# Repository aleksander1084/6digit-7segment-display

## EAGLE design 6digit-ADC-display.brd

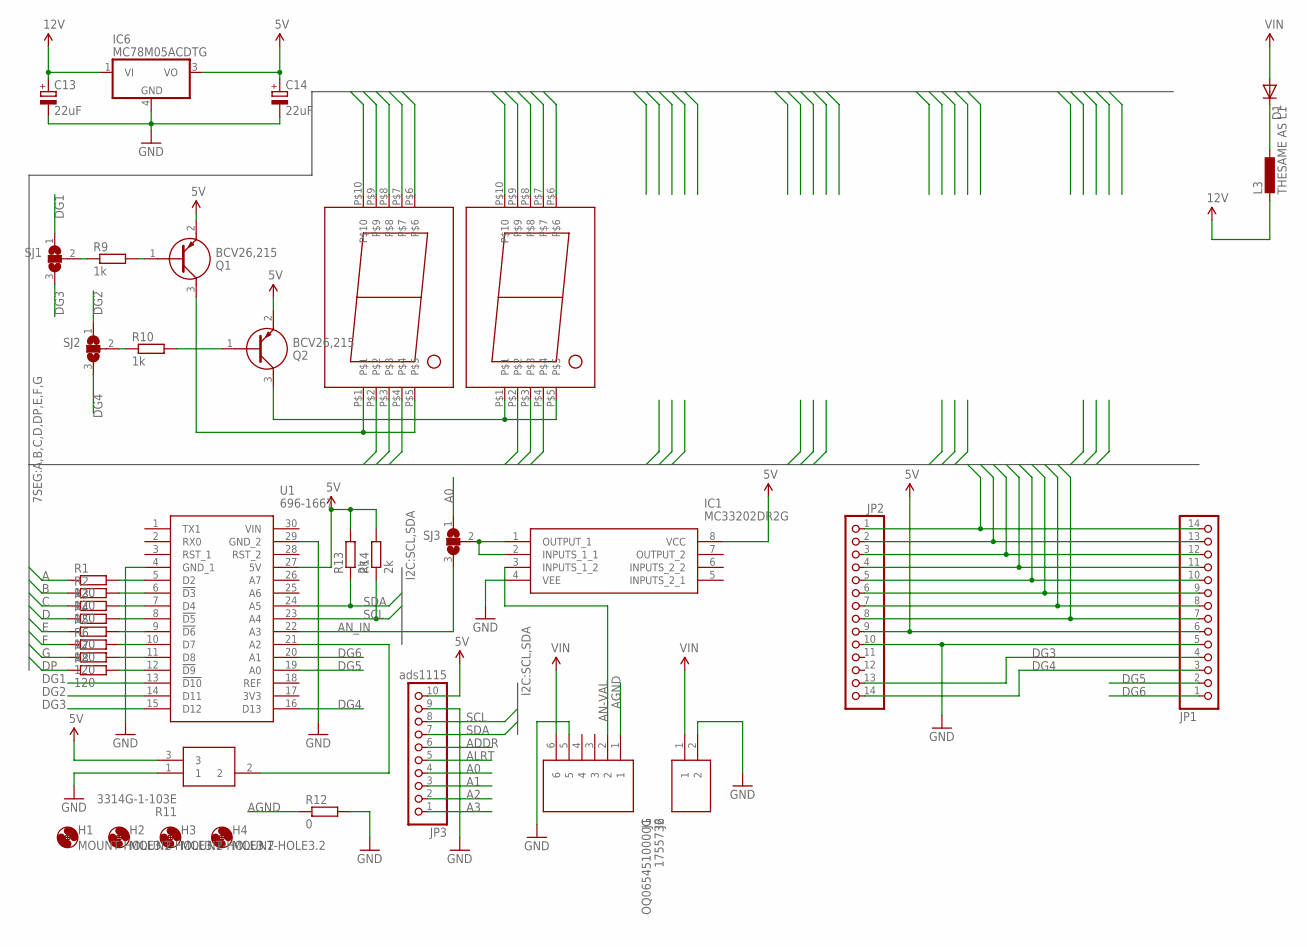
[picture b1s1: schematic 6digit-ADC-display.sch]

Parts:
C13, C14: 22uF; E2,5-7
D1: DIODE-DO-214AC; DO-214AC
H1, H2, H3, H4: MOUNT-HOLE3.2; 3,2
IC1: MC33202DR2G; SOIC127P600X175-8N
IC6: MC78M05ACDTG; DPACK_3
J1: 1755736; SHDR2W100P0X508_1X2_1216X860X1
J2: OQ0654510000G; SHDRRA6W100P0X508_1X6_3248X120
JP1, JP2: PINHD-1X14/90; 1X14/90
JP3: ads1115; 1X10
L3: THESAME AS L1; L1812
Q1, Q2: BCV26,215; SOT95P230X110-3N
R1, R2, R3, R5, R6, R7, R8: 120; R0805
R4: R-EU_R0805; R0805
R9, R10: 1k; R0805
R11: 3314G-1-103E; 3314G-1-102E
R12: 0; R0805
R13, R14: 2k; R0805
SJ1, SJ2, SJ3: SJ2W; SJ_2
U1: 696-1667; 6961667
U$1, U$2: TOS-23101BMRL-B

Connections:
5V: C14.+, IC1.8 (VCC), IC6.3 (VO), JP1.6, JP2.9, JP3.10, Q1.2 (E), Q2.2 (E), R11.3, R13.2, R14.2, U1.27 (5V)
12V: C13.+, IC6.1 (VI), L3.2
A: JP1.14, JP2.1, R1.1, U$1.P$7, U$2.P$7
A0: JP3.4, SJ3.1
A1: JP3.3
A2: JP3.2
A3: JP3.1
ADDR: JP3.6
AGND: J2.1, R12.1
ALRT: JP3.5
AN-VAL: IC1.3 (INPUTS_1_2), J2.2
AN_IN: SJ3.3, U1.22 (A3)
B: JP1.13, JP2.2, R2.1, U$1.P$6, U$2.P$6
C: JP1.12, JP2.3, R3.1, U$1.P$4, U$2.P$4
D: JP1.11, JP2.4, R4.1, U$1.P$3, U$2.P$3
DG1: SJ1.1, U1.13 (!D10)
DG2: SJ2.1, U1.14 (D11)
DG3: JP1.4, JP2.13, SJ1.3, U1.15 (D12)
DG4: JP1.3, JP2.14, SJ2.3, U1.16 (D13)
DG5: JP1.2, U1.19 (A0)
DG6: JP1.1, U1.20 (A1)
DP: JP1.7, JP2.8, R8.1, U$1.P$8, U$2.P$8
E: JP1.10, JP2.5, R5.1, U$1.P$2, U$2.P$2
F: JP1.9, JP2.6, R6.1, U$1.P$9, U$2.P$9
G: JP1.8, JP2.7, R7.1, U$1.P$10, U$2.P$10
GND: C13.-, C14.-, IC1.4 (VEE), IC6.4 (GND), J1.2, J2.5, JP1.5, JP2.10, JP3.9, R11.1, R12.2, U1.4 (GND_1), U1.29 (GND_2)
unnamed: R1.2, U1.5 (D2)
unnamed: R2.2, U1.6 (!D3)
unnamed: R3.2, U1.7 (D4)
unnamed: R4.2, U1.8 (!D5)
unnamed: R5.2, U1.9 (!D6)
unnamed: R6.2, U1.10 (D7)
unnamed: R7.2, U1.11 (D8)
unnamed: R8.2, U1.12 (!D9)
unnamed: D1.1 (C), L3.1
unnamed: Q1.1 (B), R9.2
unnamed: Q2.1 (B), R10.2
unnamed: R9.1, SJ1.2
unnamed: R10.1, SJ2.2
unnamed: Q1.3 (C), U$1.P$1, U$1.P$5
unnamed: Q2.3 (C), U$2.P$1, U$2.P$5
unnamed: IC1.1 (OUTPUT_1), IC1.2 (INPUTS_1_1), SJ3.2
unnamed: R11.2, U1.21 (A2)
SCL: JP3.8, R14.1, U1.23 (A4)
SDA: JP3.7, R13.1, U1.24 (A5)
VIN: D1.2 (A), J1.1, J2.6

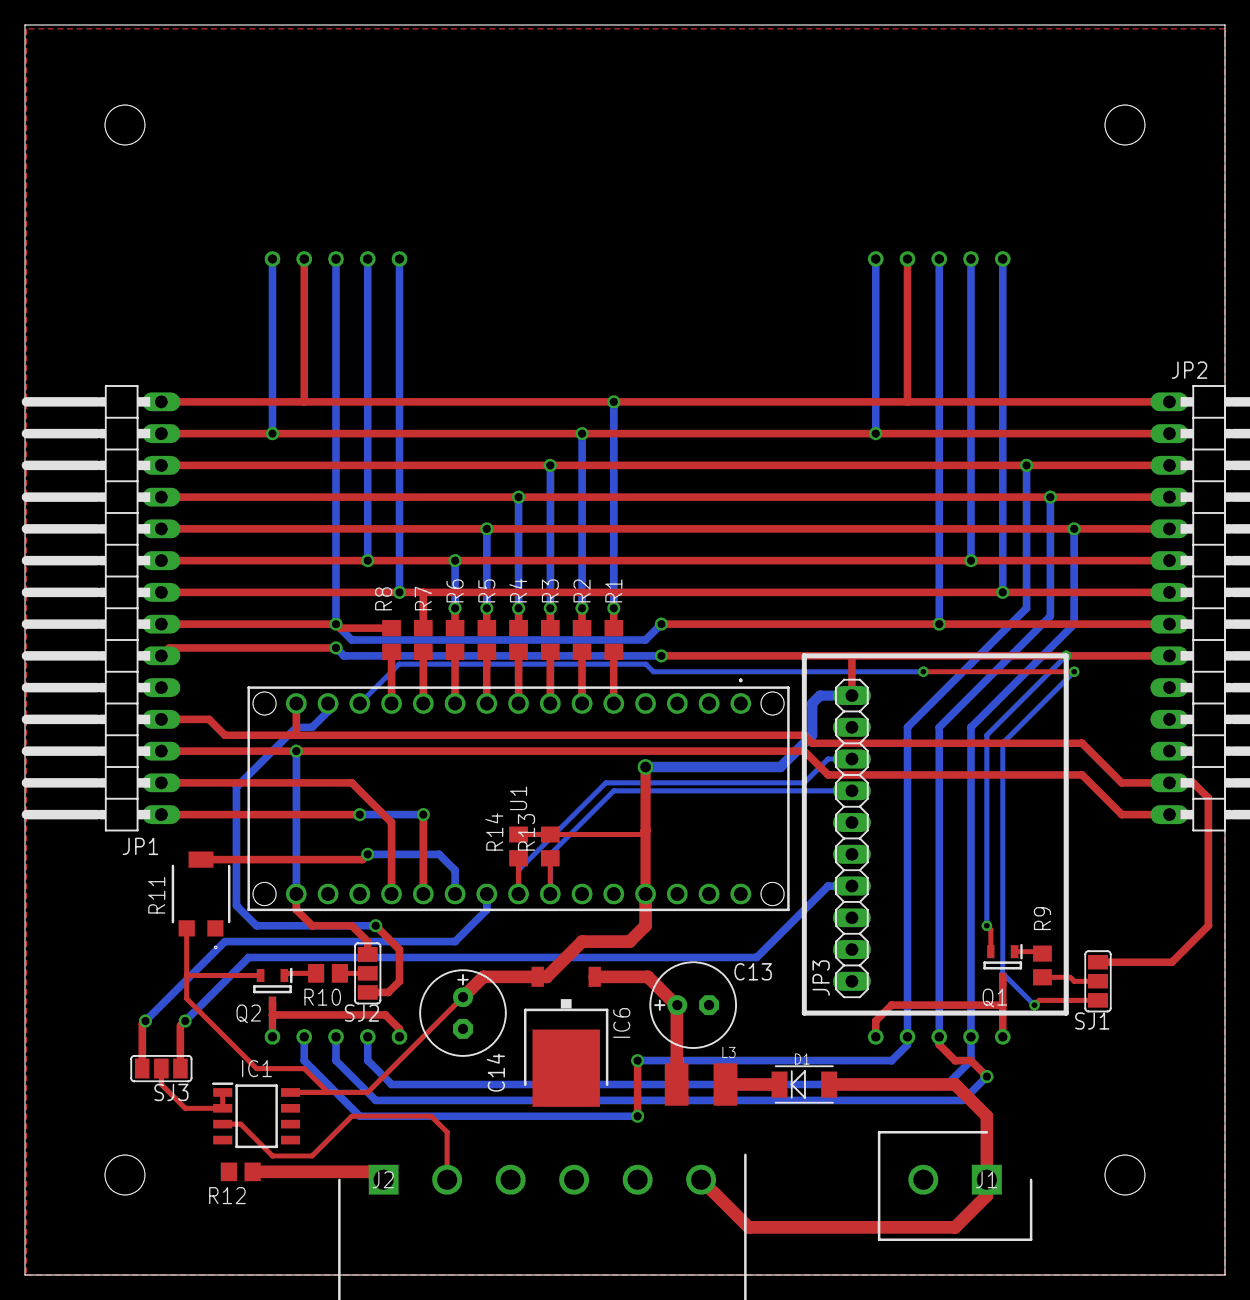
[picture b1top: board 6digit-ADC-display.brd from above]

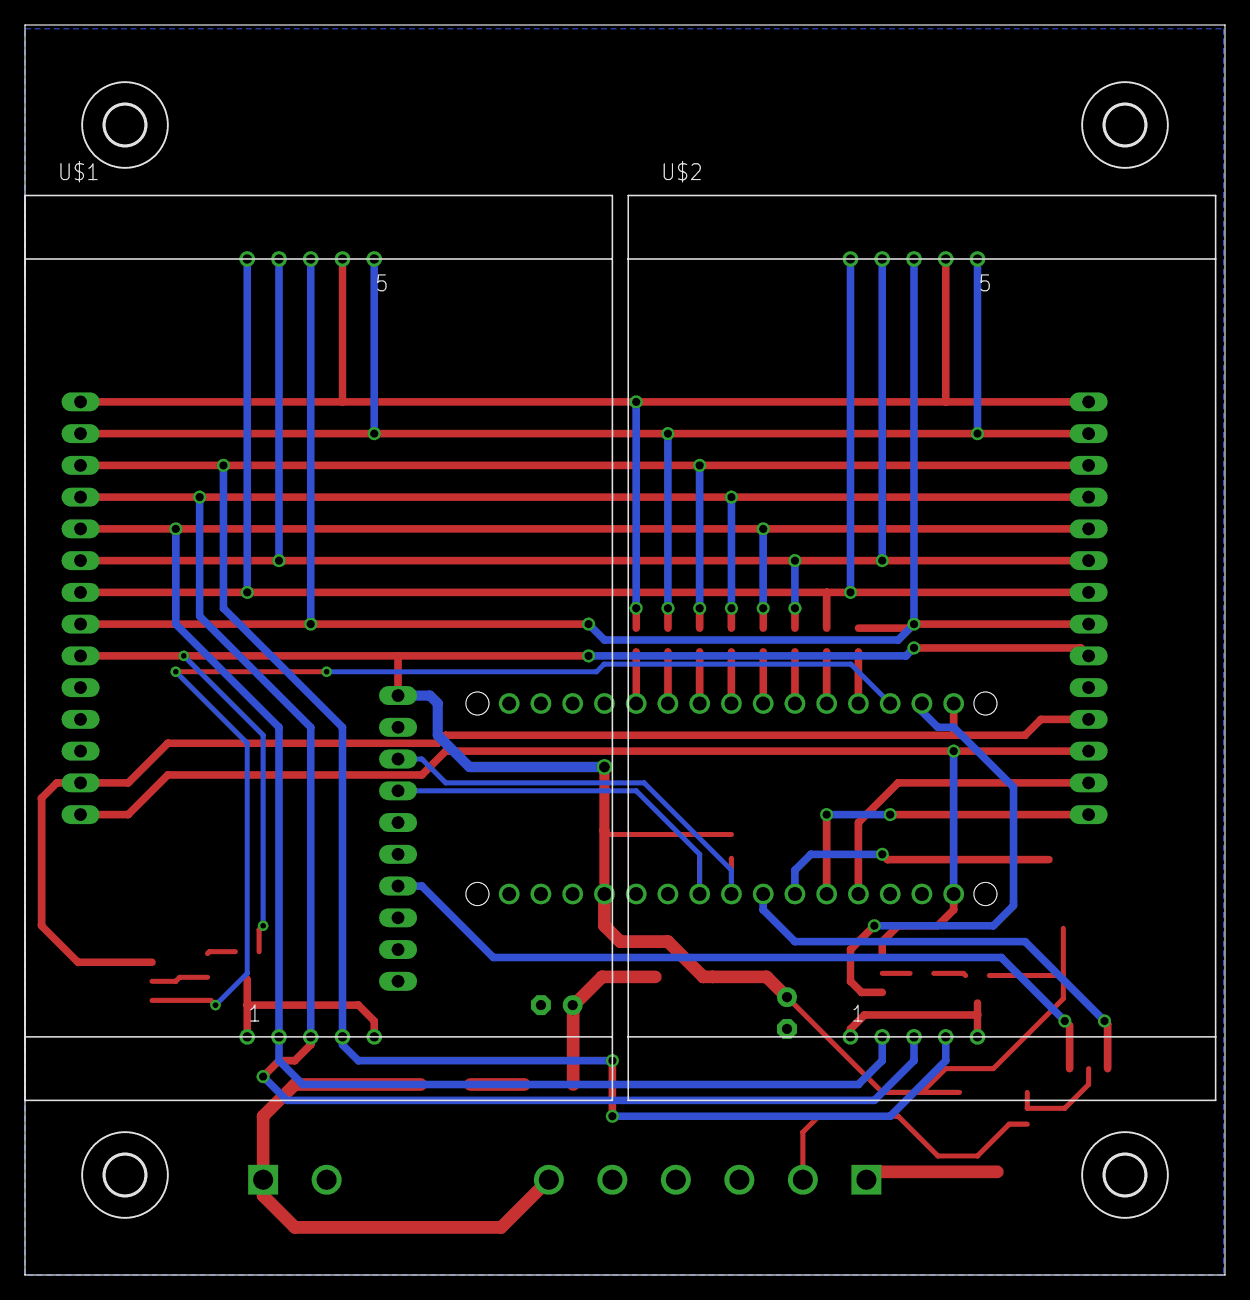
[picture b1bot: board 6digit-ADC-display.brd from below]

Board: 2 copper layers, 96.0 x 100.0 mm, 37 parts (6 on the bottom side), 41 nets.

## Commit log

2021-11-17 initial-commit
    PCB has to be updated + enclosure files have to added

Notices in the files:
parts and their libraries:
SparkFun-Aesthetics: Licensing: Creative Commons ShareAlike 4.0 International - https://creativecommons.org/licenses/by-sa/4.0
